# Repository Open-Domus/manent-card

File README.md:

# Manent card: hardware

Hardware design of the Manent card: a voice recorder with the outline of a payment card,
3.5 mm thick, that rides on the back of a phone or lies on the table in a meeting. A slide
switch starts it, a sensor lets it hear the phone it rides on, and the words reach the
phone as audio over Bluetooth LE. It is the
sibling of the ring in `manent-ring` and of the band in `manent-band`, in the form of the
Plaud Note and of Amazon's Bee Eclipse. Firmware and radio protocol live in the
`mnemo-band` repository.

Public page: [manentlabs.it/en/card/](https://manentlabs.it/en/card/) (English), [manentlabs.it/card/](https://manentlabs.it/card/) (Italian).

Nothing here has been built or measured. This is a first design on paper, checked by
scripts. Its choices are made and each says what would overturn it.

| What | Where |
| --- | --- |
| Design document: requirements, architecture, decisions | [docs/design.md](docs/design.md) |
| Does it fit? Card, the two stacks, cell, board area | [docs/space-budget.md](docs/space-budget.md) |
| How long does it last? | [docs/power-budget.md](docs/power-budget.md) |
| What it costs to make | [docs/cost-estimate.md](docs/cost-estimate.md) |
| Design review: what was checked, what was wrong, what is at risk | [docs/review.md](docs/review.md) |
| What the firmware must do for this hardware | [docs/firmware-requirements.md](docs/firmware-requirements.md) |
| What was decided and why, what is unknown, and what would settle it | [docs/open-questions.md](docs/open-questions.md) |
| Parts with sizes and how far each is verified | [parts/parts.yaml](parts/parts.yaml) |
| Circuit, as data | [electrical/gen/design.py](electrical/gen/design.py) |
| Schematic (KiCad 10), PDF, bill of materials | `electrical/kicad/`, `electrical/out/` |
| Board: placed and routed by script, no rule broken, nothing open | `electrical/kicad/card.kicad_pcb`, `electrical/out/board-*.svg` |
| Fit model, drawings, STEP | `mechanical/`, `mechanical/out/` |

## Build

Needs `uv`, and either KiCad 10 or Docker (`docker pull kicad/kicad:10.0`).

```
make all        # schematic, board, checks, tests, fit report, drawings, budgets, STEP
make test       # tests only
make route      # route the board again: needs Java and Freerouting, see tools/route.sh
```

The schematic and the board are generated: edit `electrical/gen/design.py` and the fit
model, never the `.kicad_sch` or `.kicad_pcb` files.
Every pin carries a label with its net name instead of drawn wires. `make schematic` runs
KiCad's rule check and compares the netlist KiCad reads with the one in `design.py`.

The board is placed and routed by script. `make board` rebuilds it from the route kept in
`electrical/kicad/card.ses`; after a change to the circuit or the placement that route no
longer fits and `make route` must be run. Nobody has reviewed the routing by eye.

## Licences

Hardware and the scripts that generate it under CERN-OHL-S v2 (`LICENSE`), documents under
CC BY-SA 4.0 (`LICENSE-docs`).

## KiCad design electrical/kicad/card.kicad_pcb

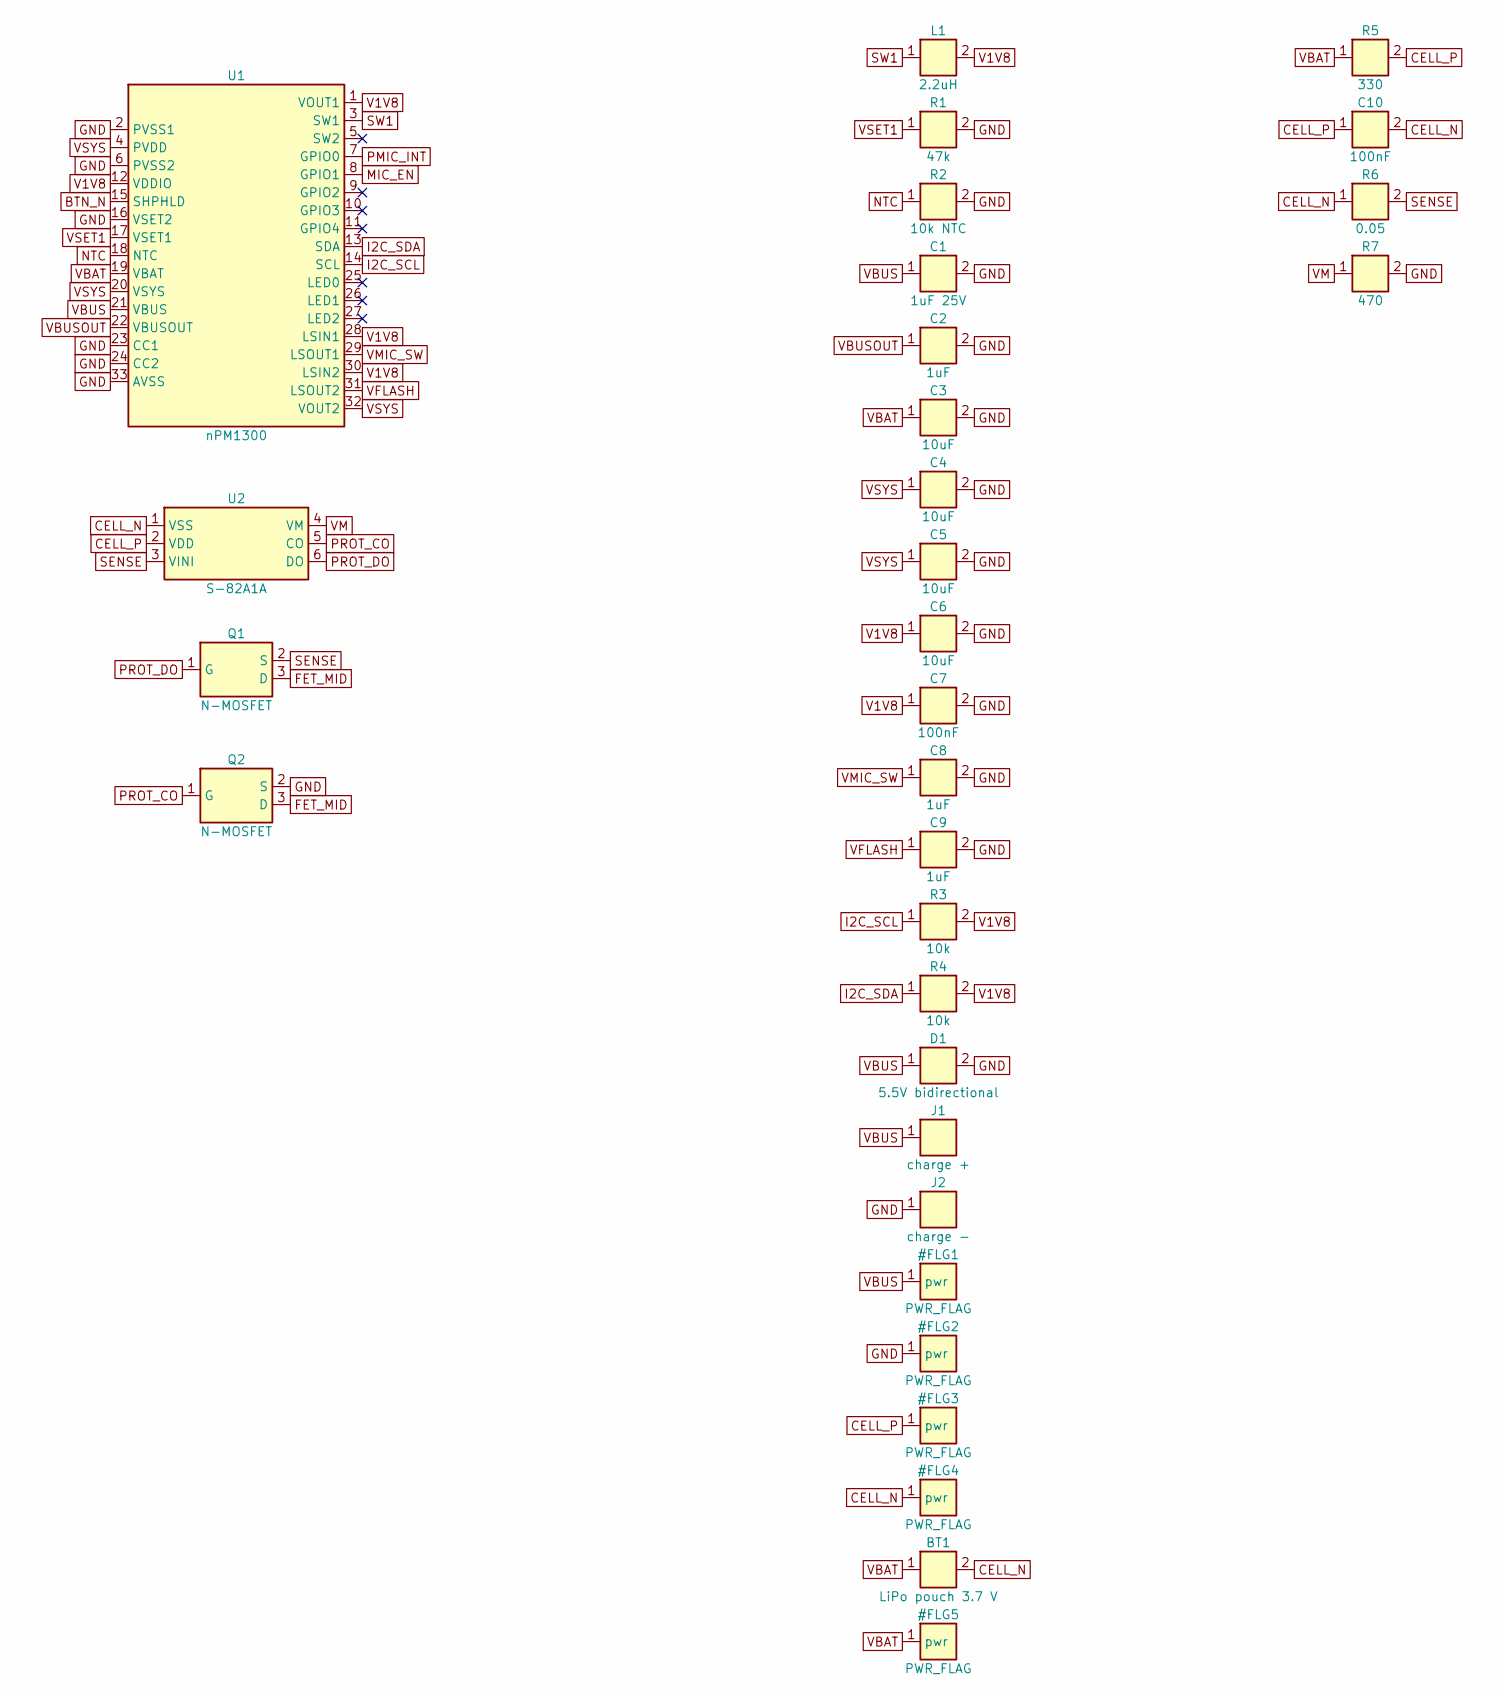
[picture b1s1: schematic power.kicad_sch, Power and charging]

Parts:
BT1: LiPo pouch 3.7 V; Cell_Tabs; MPN 203580 class
C1: 1uF 25V; C_0603_1608Metric
C2, C8, C9: 1uF; C_0402_1005Metric
C3, C4, C5, C6: 10uF; C_0603_1608Metric
C7, C10: 100nF; C_0402_1005Metric
D1: 5.5V bidirectional; D_0201_0603Metric; MPN ESD230-B1-W0201
J1: charge +; Pad_Contact_D2.0
J2: charge -; Pad_Contact_D2.0
L1: 2.2uH; L_0805_2012Metric; MPN VLS201610HBX-2R2M-1
Q1, Q2: N-MOSFET; SOT-883; MPN PMZB290UNE2
R1: 47k; R_0402_1005Metric
R2: 10k NTC; R_0402_1005Metric; MPN to choose
R3, R4: 10k; R_0402_1005Metric
R5: 330; R_0402_1005Metric
R6: 0.05; R_0402_1005Metric
R7: 470; R_0402_1005Metric
U1: nPM1300; QFN-32-1EP_5x5mm_P0.5mm_EP3.45x3.45mm; MPN nPM1300-QEAA-R7
U2: S-82A1A; DFN-6_1414; MPN S-82A1AAG-A6T5S (variant to confirm)

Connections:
BTN_N: U1.15 (SHPHLD); also elsewhere on the board
CELL_N: BT1.2, C10.2, R6.1, U2.1 (VSS)
CELL_P: C10.1, R5.2, U2.2 (VDD)
FET_MID: Q1.3 (D), Q2.3 (D)
GND: C1.2, C2.2, C3.2, C4.2, C5.2, C6.2, C7.2, C8.2, C9.2, D1.2, J2.1, Q2.2 (S), R1.2, R2.2, R7.2, U1.2 (PVSS1), U1.6 (PVSS2), U1.16 (VSET2), U1.23 (CC1), U1.24 (CC2), U1.33 (AVSS); also elsewhere on the board
I2C_SCL: R3.1, U1.14 (SCL); also elsewhere on the board
I2C_SDA: R4.1, U1.13 (SDA); also elsewhere on the board
MIC_EN: U1.8 (GPIO1); also elsewhere on the board
NTC: R2.1, U1.18 (NTC)
PMIC_INT: U1.7 (GPIO0); also elsewhere on the board
PROT_CO: Q2.1 (G), U2.5 (CO)
PROT_DO: Q1.1 (G), U2.6 (DO)
SENSE: Q1.2 (S), R6.2, U2.3 (VINI)
SW1: L1.1, U1.3 (SW1)
V1V8: C6.1, C7.1, L1.2, R3.2, R4.2, U1.1 (VOUT1), U1.12 (VDDIO), U1.28 (LSIN1), U1.30 (LSIN2); also elsewhere on the board
VBAT: BT1.1, C3.1, R5.1, U1.19 (VBAT); also elsewhere on the board
VBUS: C1.1, D1.1, J1.1, U1.21 (VBUS); also elsewhere on the board
VBUSOUT: C2.1, U1.22 (VBUSOUT)
VFLASH: C9.1, U1.31 (LSOUT2); also elsewhere on the board
VM: R7.1, U2.4 (VM)
VMIC_SW: C8.1, U1.29 (LSOUT1); also elsewhere on the board
VSET1: R1.1, U1.17 (VSET1)
VSYS: C4.1, C5.1, U1.4 (PVDD), U1.20 (VSYS), U1.32 (VOUT2); also elsewhere on the board

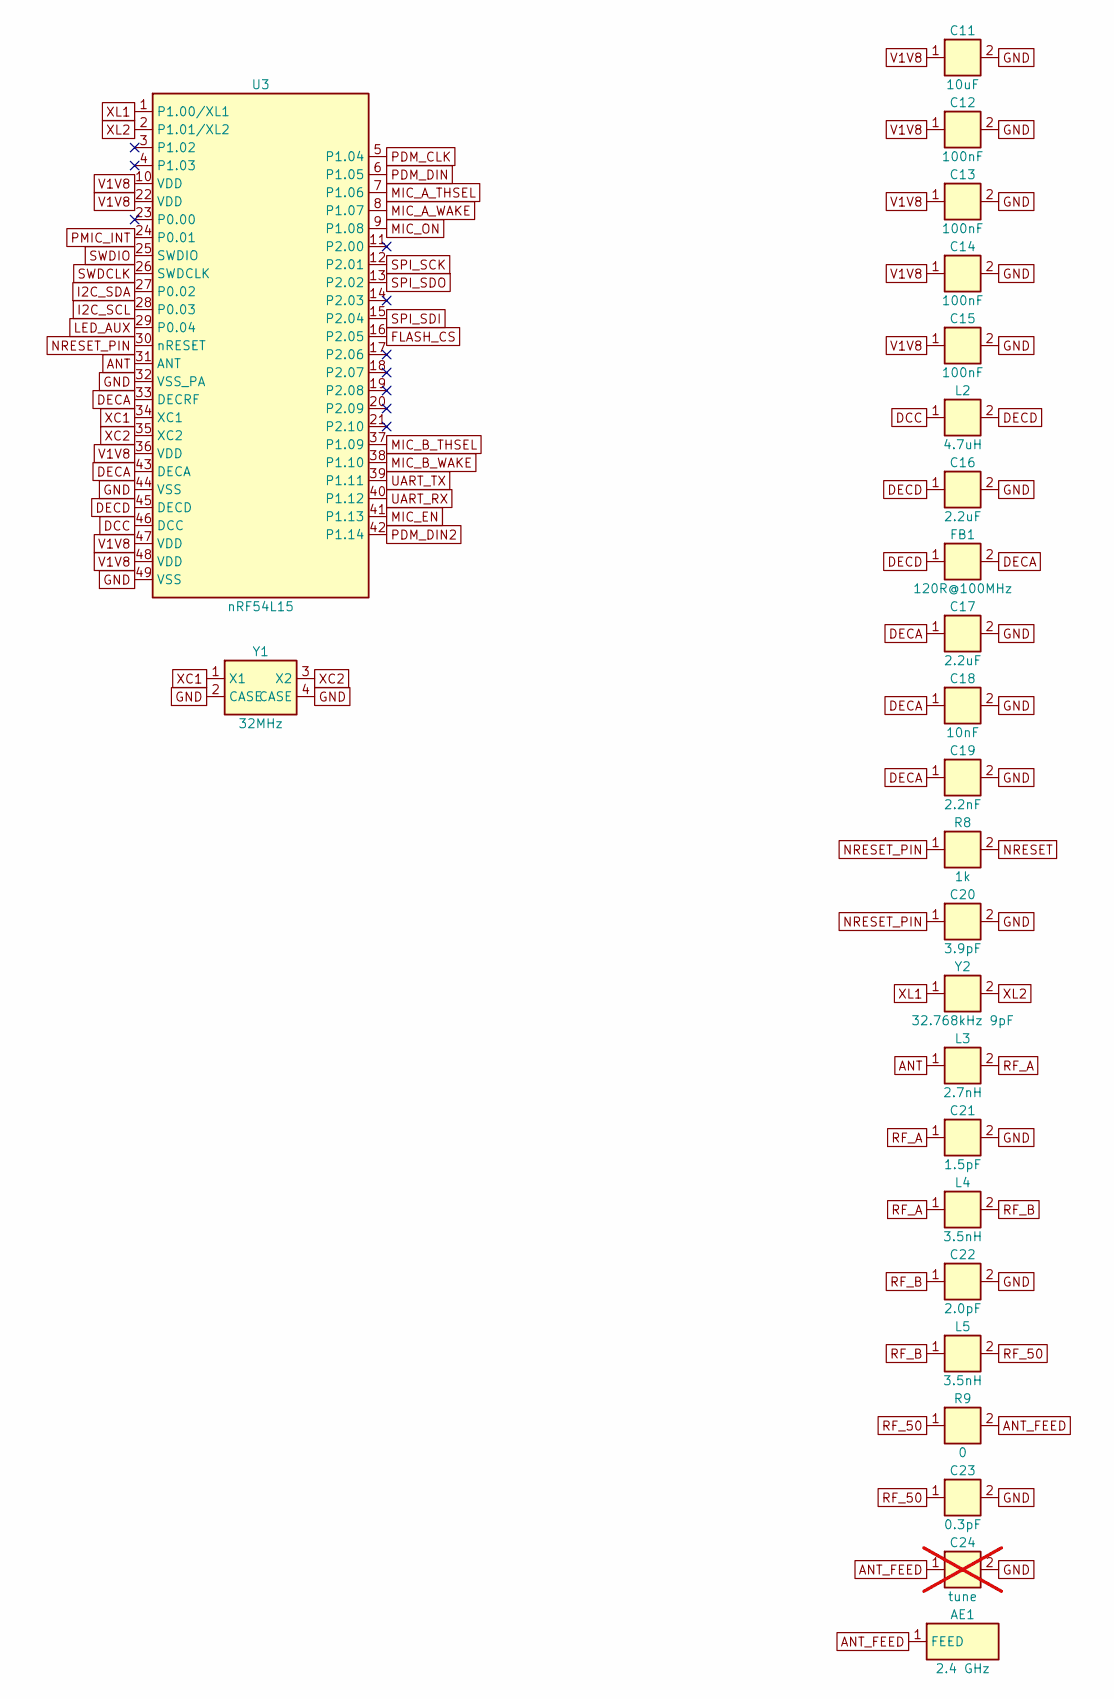
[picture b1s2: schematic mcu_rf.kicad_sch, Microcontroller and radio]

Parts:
AE1: 2.4 GHz; Antenna_1608; MPN ANT1608LL14R2400A
C11: 10uF; C_0603_1608Metric
C12, C13, C14, C15: 100nF; C_0201_0603Metric
C16, C17: 2.2uF; C_0201_0603Metric
C18: 10nF; C_0201_0603Metric
C19: 2.2nF; C_0201_0603Metric
C20: 3.9pF; C_0201_0603Metric
C21: 1.5pF; C_0201_0603Metric; MPN GJM0335C1E1R5WB01
C22: 2.0pF; C_0201_0603Metric; MPN GJM0335C1E2R0WB01
C23: 0.3pF; C_0201_0603Metric
C24: tune; C_0201_0603Metric; not fitted
FB1: 120R@100MHz; L_0201_0603Metric; MPN BLM03AG121SN1D
L2: 4.7uH; L_0402_1005Metric; MPN PLEA67BCA4R7M-1PT00
L3: 2.7nH; L_0201_0603Metric; MPN LQP03HQ2N7B02
L4, L5: 3.5nH; L_0201_0603Metric; MPN LQP03HQ3N5B02
R8: 1k; R_0201_0603Metric
R9: 0; R_0201_0603Metric
U3: nRF54L15; QFN-48-1EP_6x6mm_P0.4mm_EP4.6x4.6mm; MPN nRF54L15-QFAA-R
Y1: 32MHz; Crystal_SMD_2016-4Pin_2.0x1.6mm; MPN CX2016DB32000D0FLJCC
Y2: 32.768kHz 9pF; Crystal_SMD_2012-2Pin_2.0x1.2mm; MPN 9HT11-32.768KDZC-T

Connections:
ANT: L3.1, U3.31 (ANT)
ANT_FEED: AE1.1, C24.1, R9.2
DCC: L2.1, U3.46 (DCC)
DECA: C17.1, C18.1, C19.1, FB1.2, U3.33 (DECRF), U3.43 (DECA)
DECD: C16.1, FB1.1, L2.2, U3.45 (DECD)
FLASH_CS: U3.16 (P2.05); also elsewhere on the board
GND: C11.2, C12.2, C13.2, C14.2, C15.2, C16.2, C17.2, C18.2, C19.2, C20.2, C21.2, C22.2, C23.2, C24.2, U3.32 (VSS_PA), U3.44 (VSS), U3.49 (VSS), Y1.2 (CASE), Y1.4 (CASE); also elsewhere on the board
I2C_SCL: U3.28 (P0.03); also elsewhere on the board
I2C_SDA: U3.27 (P0.02); also elsewhere on the board
LED_AUX: U3.29 (P0.04); also elsewhere on the board
MIC_A_THSEL: U3.7 (P1.06); also elsewhere on the board
MIC_A_WAKE: U3.8 (P1.07); also elsewhere on the board
MIC_B_THSEL: U3.37 (P1.09); also elsewhere on the board
MIC_B_WAKE: U3.38 (P1.10); also elsewhere on the board
MIC_EN: U3.41 (P1.13); also elsewhere on the board
MIC_ON: U3.9 (P1.08); also elsewhere on the board
NRESET: R8.2; also elsewhere on the board
NRESET_PIN: C20.1, R8.1, U3.30 (nRESET)
PDM_CLK: U3.5 (P1.04); also elsewhere on the board
PDM_DIN: U3.6 (P1.05); also elsewhere on the board
PDM_DIN2: U3.42 (P1.14); also elsewhere on the board
PMIC_INT: U3.24 (P0.01); also elsewhere on the board
RF_50: C23.1, L5.2, R9.1
RF_A: C21.1, L3.2, L4.1
RF_B: C22.1, L4.2, L5.1
SPI_SCK: U3.12 (P2.01); also elsewhere on the board
SPI_SDI: U3.15 (P2.04); also elsewhere on the board
SPI_SDO: U3.13 (P2.02); also elsewhere on the board
SWDCLK: U3.26 (SWDCLK); also elsewhere on the board
SWDIO: U3.25 (SWDIO); also elsewhere on the board
UART_RX: U3.40 (P1.12); also elsewhere on the board
UART_TX: U3.39 (P1.11); also elsewhere on the board
V1V8: C11.1, C12.1, C13.1, C14.1, C15.1, U3.10 (VDD), U3.22 (VDD), U3.36 (VDD), U3.47 (VDD), U3.48 (VDD); also elsewhere on the board
XC1: U3.34 (XC1), Y1.1 (X1)
XC2: U3.35 (XC2), Y1.3 (X2)
XL1: U3.1 (P1.00/XL1), Y2.1
XL2: U3.2 (P1.01/XL2), Y2.2

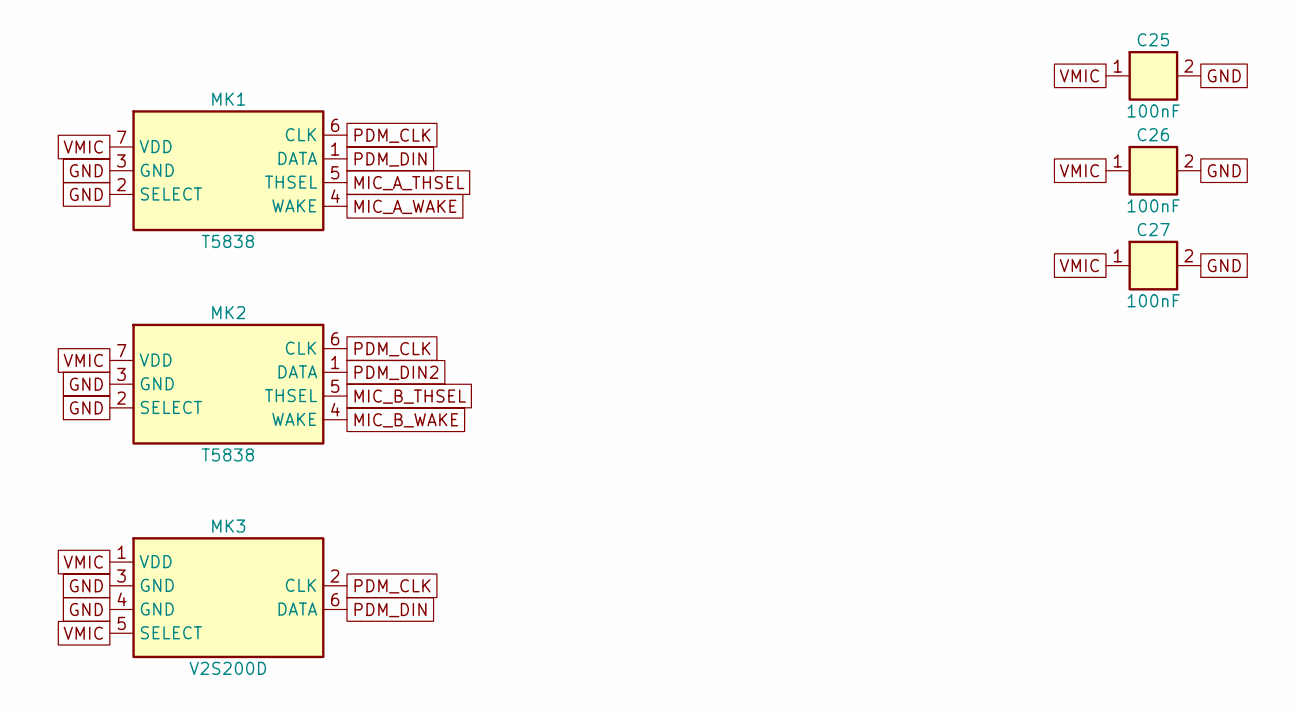
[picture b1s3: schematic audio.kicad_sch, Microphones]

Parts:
C25, C26, C27: 100nF; C_0201_0603Metric
MK1, MK2: T5838; MPN MMICT5838-00-012
MK3: V2S200D; MPN V2S200D

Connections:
GND: C25.2, C26.2, C27.2, MK1.2 (SELECT), MK1.3 (GND), MK2.2 (SELECT), MK2.3 (GND), MK3.3 (GND), MK3.4 (GND); also elsewhere on the board
MIC_A_THSEL: MK1.5 (THSEL); also elsewhere on the board
MIC_A_WAKE: MK1.4 (WAKE); also elsewhere on the board
MIC_B_THSEL: MK2.5 (THSEL); also elsewhere on the board
MIC_B_WAKE: MK2.4 (WAKE); also elsewhere on the board
PDM_CLK: MK1.6 (CLK), MK2.6 (CLK), MK3.2 (CLK); also elsewhere on the board
PDM_DIN: MK1.1 (DATA), MK3.6 (DATA); also elsewhere on the board
PDM_DIN2: MK2.1 (DATA); also elsewhere on the board
VMIC: C25.1, C26.1, C27.1, MK1.7 (VDD), MK2.7 (VDD), MK3.1 (VDD), MK3.5 (SELECT); also elsewhere on the board

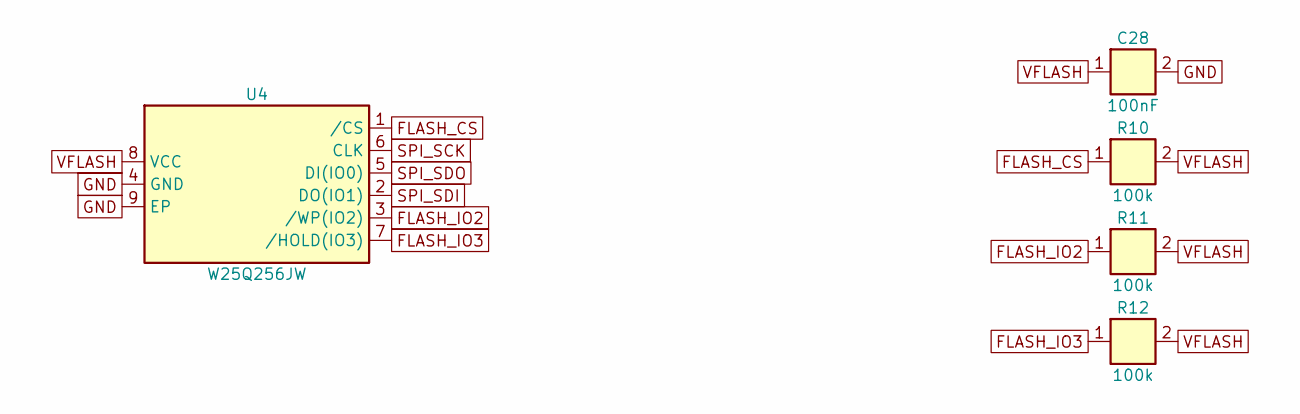
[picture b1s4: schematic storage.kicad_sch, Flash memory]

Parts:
C28: 100nF; C_0402_1005Metric
R10, R11, R12: 100k; R_0402_1005Metric
U4: W25Q256JW; WSON-8-1EP_8x6mm_P1.27mm_EP3.4x4.3mm; MPN W25Q256JWEIQ

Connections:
FLASH_CS: R10.1, U4.1 (/CS); also elsewhere on the board
FLASH_IO2: R11.1, U4.3 (/WP(IO2))
FLASH_IO3: R12.1, U4.7 (/HOLD(IO3))
GND: C28.2, U4.4 (GND), U4.9 (EP); also elsewhere on the board
SPI_SCK: U4.6 (CLK); also elsewhere on the board
SPI_SDI: U4.2 (DO(IO1)); also elsewhere on the board
SPI_SDO: U4.5 (DI(IO0)); also elsewhere on the board
VFLASH: C28.1, R10.2, R11.2, R12.2, U4.8 (VCC); also elsewhere on the board

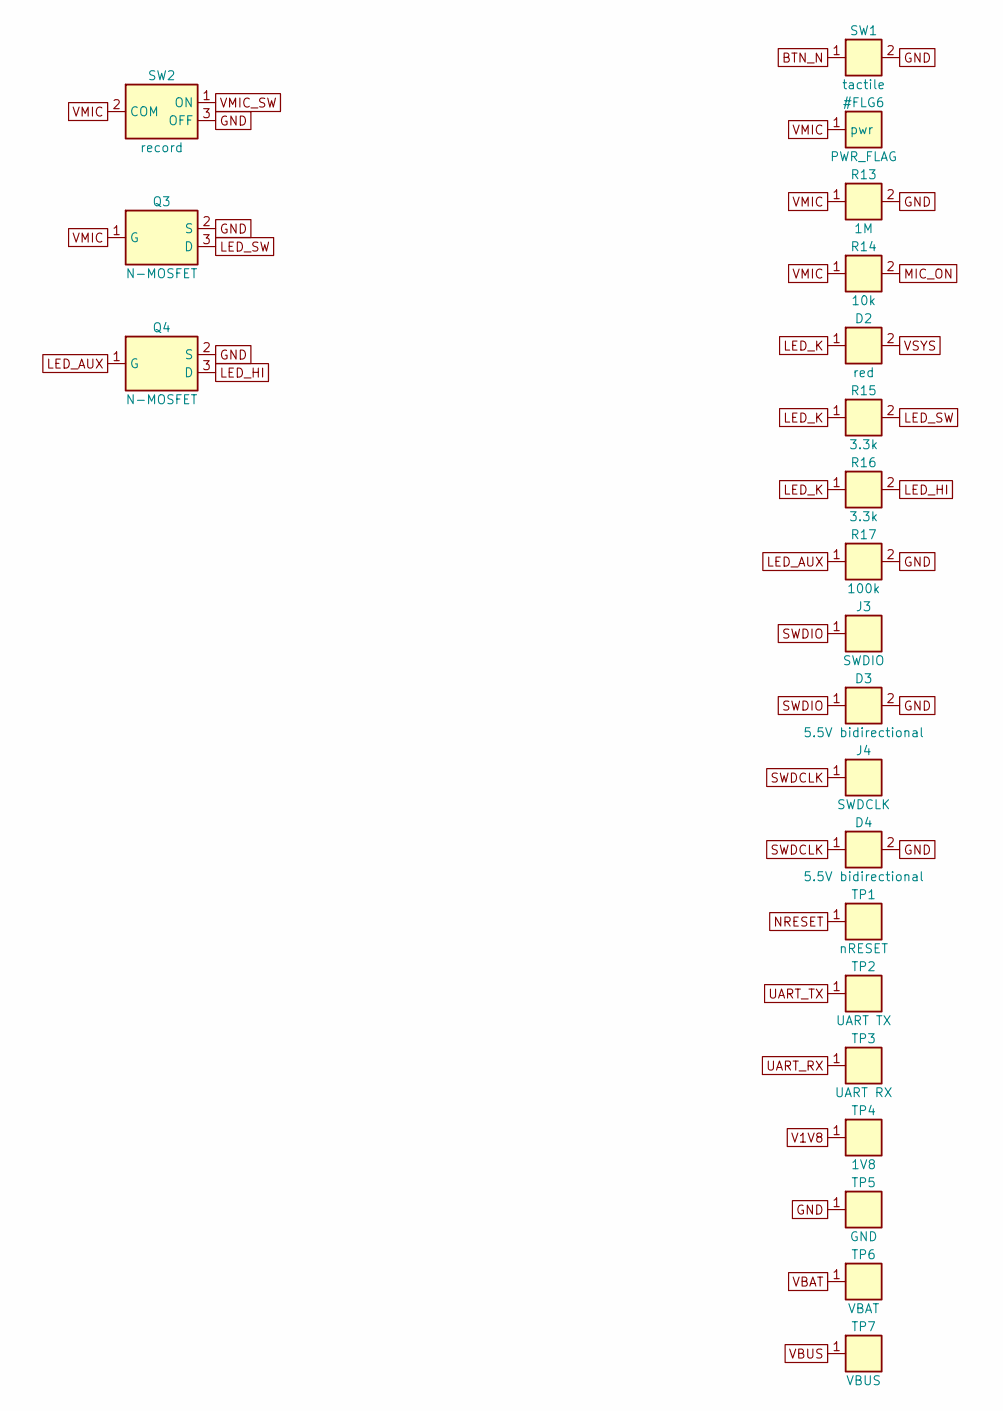
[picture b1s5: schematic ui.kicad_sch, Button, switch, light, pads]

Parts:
D2: red; LED_156125RS75000; MPN 156125RS75000
D3, D4: 5.5V bidirectional; D_0201_0603Metric; MPN ESD230-B1-W0201
J3: SWDIO; Pad_Contact_D2.0
J4: SWDCLK; Pad_Contact_D2.0
Q3, Q4: N-MOSFET; SOT-883; MPN PMZB290UNE2
R13: 1M; R_0402_1005Metric
R14: 10k; R_0402_1005Metric
R15, R16: 3.3k; R_0402_1005Metric
R17: 100k; R_0402_1005Metric
SW1: tactile; EVQP7J; MPN EVQP7J01P
SW2: record; SSSS811101; MPN SSSS811101
TP1: nRESET; Pad_Test_D1.0
TP2: UART TX; Pad_Test_D1.0
TP3: UART RX; Pad_Test_D1.0
TP4: 1V8; Pad_Test_D1.0
TP5: GND; Pad_Test_D1.0
TP6: VBAT; Pad_Test_D1.0
TP7: VBUS; Pad_Test_D1.0

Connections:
BTN_N: SW1.1; also elsewhere on the board
GND: D3.2, D4.2, Q3.2 (S), Q4.2 (S), R13.2, R17.2, SW1.2, SW2.3 (OFF), TP5.1; also elsewhere on the board
LED_AUX: Q4.1 (G), R17.1; also elsewhere on the board
LED_HI: Q4.3 (D), R16.2
LED_K: D2.1, R15.1, R16.1
LED_SW: Q3.3 (D), R15.2
MIC_ON: R14.2; also elsewhere on the board
NRESET: TP1.1; also elsewhere on the board
SWDCLK: D4.1, J4.1; also elsewhere on the board
SWDIO: D3.1, J3.1; also elsewhere on the board
UART_RX: TP3.1; also elsewhere on the board
UART_TX: TP2.1; also elsewhere on the board
V1V8: TP4.1; also elsewhere on the board
VBAT: TP6.1; also elsewhere on the board
VBUS: TP7.1; also elsewhere on the board
VMIC: Q3.1 (G), R13.1, R14.1, SW2.2 (COM); also elsewhere on the board
VMIC_SW: SW2.1 (ON); also elsewhere on the board
VSYS: D2.2; also elsewhere on the board

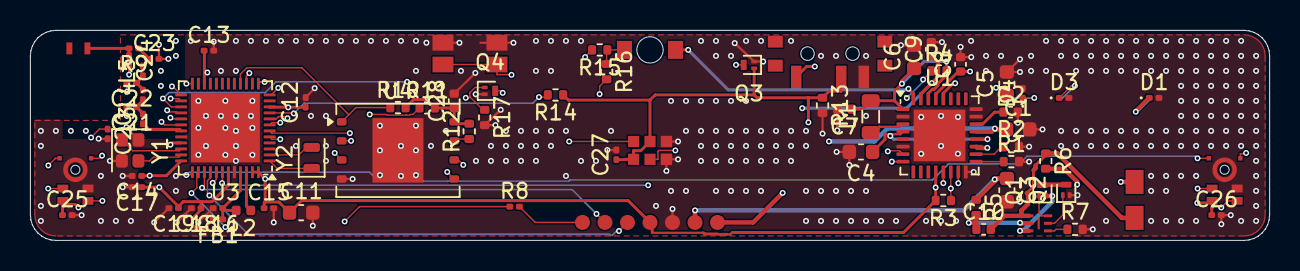
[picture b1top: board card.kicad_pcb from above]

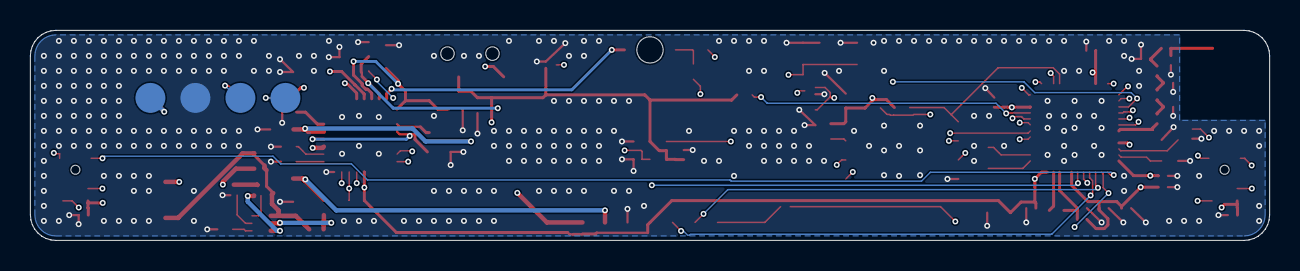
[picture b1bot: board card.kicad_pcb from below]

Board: 4 copper layers, 82.6 x 14.0 mm, 83 parts (4 on the bottom side), 60 nets.

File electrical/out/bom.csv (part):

References,Quantity,Value,Manufacturer,Part number,Package,Fitted,Notes
U1,1,nPM1300,Nordic Semiconductor,nPM1300-QEAA-R7,"QFN-32 5x5, 0.5 mm pitch",yes,"The band's nPM1304 stops at 100 mA; this one charges at 32 to 800 mA and has the same 32 pins. Set about 225 mA, half the cell's capacity per hour. BUCK2 unused as in Nordic's reference configuration 2 (nPM1304 layout files; the same in the nPM1300's): VSET2 grounded, SW2 open, VOUT2 to VSYS. LED0-2, GPIO2-4 left open: not confirmed. CC1 and CC2 grounded: the input limit starts at 100 mA and firmware must raise it each time the charger is connected"
L1,1,2.2uH,TDK,VLS201610HBX-2R2M-1,0806,yes,"Nordic asks for DCR under 0.4 ohm in 0806 (2.0 x 1.6 mm); this one is 0.17 max, 1.45 A, 1.0 tall. The same part on the band, the card and the pendant"
R1,1,47k,,,0402,yes,Sets BUCK1 to 1.8 V at power-on
R2,1,10k NTC,,to choose,0402,yes,"Thermistor, B about 3380 K, placed by the cell tabs: stops the charge when the closed card is too warm or too cold"
C1,1,1uF 25V,,,0603,yes,"As Nordic's nPM1304-QEAA reference layout 1.0, configuration 2, the sibling chip with the same pins"
C2 C8 C9,3,1uF,,,0402,yes,"As Nordic's nPM1304-QEAA reference layout 1.0, configuration 2, the sibling chip with the same pins | Load switch output, before the recording switch. As Nordic's nPM1304-QEAA reference layout 1.0, configuration 2, the sibling chip with the same pins | Load switch output. As Nordic's nPM1304-QEAA reference layout 1.0, configuration 2, the sibling chip with the same pins"
C3 C4 C5 C6 C11,5,10uF,,,0603,yes,"The nPM1304 reference has 2.2 uF here; kept at 10 uF for this card's 225 mA charge until the nPM1300's layout files are read | Buck input, at PVDD and PVSS1. As Nordic's nPM1304-QEAA reference layout 1.0, configuration 2, the sibling chip with the same pins | VSYS output. As Nordic's nPM1304-QEAA reference layout 1.0, configuration 2, the sibling chip with the same pins | Buck output: at least 4 uF effective. As Nordic's nPM1304-QEAA reference layout 1.0, configuration 2, the sibling chip with the same pins"
C7 C10 C28,3,100nF,,,0402,yes,VDDIO
R3 R4 R14,3,10k,,,0402,yes,"Lets the SoC read the switch and wake on it. With the switch off the rail is grounded, so this pin cannot power the microphones"
D1 D3 D4,3,5.5V bidirectional,Infineon,ESD230-B1-W0201,0201,yes,Fingers reach this pad. Its capacitance on a debug line is to confirm
J1,1,charge +,,,2 mm pad,yes,"Copper on the bare face of the board, behind a window in the front skin, at one end only: a card laid on its charger the wrong way round touches nothing"
J2,1,charge -,,,2 mm pad,yes,
BT1,1,LiPo pouch 3.7 V,to choose,203580 class,,yes,Size and capacity depend on the card; see docs/space-budget.md
R5,1,330,,,0402,yes,Protector supply filter
U2,1,S-82A1A,ABLIC,S-82A1AAG-A6T5S (variant to confirm),DFN-6 1.4x1.4,yes,Fit only if the cell has no protection of its own; thresholds to match the charge voltage
R6,1,0.05,,,0402,yes,"Overcurrent sense: about 1 A trip if the threshold is 50 mV (calculated, not from a datasheet). The band's 0.25 ohm would trip at 200 mA, below this card's 225 mA charge"
R7,1,470,,,0402,yes,
Q1 Q2 Q3 Q4,4,N-MOSFET,Nexperia,PMZB290UNE2,DFN1006B-3,yes,"Discharge FET; two singles with their drains joined. The same FET in all eight places of the four products | Charge FET | Gate is the microphone rail: the light is on whenever the microphones have power. Vgs(th) under 1 V | Firmware can only add light, never remove the recording light"
U3,1,nRF54L15,Nordic Semiconductor,nRF54L15-QFAA-R,"QFN-48 6x6, 0.4 mm pitch",yes,Pin 49 is the exposed pad: ground
C12 C13 C14 C15 C25 C26 C27,7,100nF,,,0201,yes,"One next to each side's VDD pin. As Nordic's nRF54L15-QFAA reference layout 0.8 | X7R, next to pin 7 of microphone A | X7R, next to pin 7 of microphone B | C0G, next to the supply pin of the call sensor: its maker asks for no class 2 ceramic nearby, which sings"
L2,1,4.7uH,TDK,PLEA67BCA4R7M-1PT00,0402,yes,"DC/DC inductor, the ring's part. Nordic's QFN reference takes a 0603 of 0.65 ohm and 120 mA; this one is 1.08 ohm max"
C16 C17,2,2.2uF,,,0201,yes,As Nordic's nRF54L15-QFAA reference layout 0.8
FB1,1,120R@100MHz,Murata,BLM03AG121SN1D,0201,yes,"The reference asks 120 ohm at 100 MHz, 200 mA, 0.5 ohm max: the ring's part"
C18,1,10nF,,,0201,yes,As Nordic's nRF54L15-QFAA reference layout 0.8
C19,1,2.2nF,,,0201,yes,X7R. As Nordic's nRF54L15-QFAA reference layout 0.8
R8,1,1k,,,0201,yes,"Filter on the reset pin, next to the antenna pin. As Nordic's nRF54L15-QFAA reference layout 0.8"
C20,1,3.9pF,,,0201,yes,"C0G, at the reset pin. As Nordic's nRF54L15-QFAA reference layout 0.8"
Y1,1,32MHz,Kyocera,CX2016DB32000D0FLJCC,2016,yes,"2.0 x 1.6 mm, 8 pF, 10 ppm, as the reference asks (8 pF, 40 ppm in all); pads 2 and 4 are the lid, grounded: check against its drawing. Load capacitors are inside the chip"
Y2,1,32.768kHz 9pF,TXC,9HT11-32.768KDZC-T,2012,yes,"Fitted, unlike on the ring: the card stays connected for weeks and there is room. Load capacitors are inside the chip"
L3,1,2.7nH,Murata,LQP03HQ2N7B02,0201,yes,Matching network. As Nordic's nRF54L15-QFAA reference layout 0.8
C21,1,1.5pF,Murata,GJM0335C1E1R5WB01,0201,yes,Matching network. As Nordic's nRF54L15-QFAA reference layout 0.8
L4 L5,2,3.5nH,Murata,LQP03HQ3N5B02,0201,yes,Matching network. As Nordic's nRF54L15-QFAA reference layout 0.8
C22,1,2.0pF,Murata,GJM0335C1E2R0WB01,0201,yes,Matching network. As Nordic's nRF54L15-QFAA reference layout 0.8
R9,1,0,,,0201,yes,"Antenna tuning, series: value from measurement in a closed card, alone and on a phone"
C23,1,0.3pF,,,0201,yes,"C0G, 0.1 pF tolerance: the last part of the matching network. As Nordic's nRF54L15-QFAA reference layout 0.8"
C24,1,tune,,,0201,no,"Antenna tuning, shunt"
AE1,1,2.4 GHz,Yageo,ANT1608LL14R2400A,1608 chip antenna,yes,Chip antenna or printed trace in the corner of the board; decided with the first radio measurements
MK1 MK2,2,T5838,TDK InvenSense,MMICT5838-00-012,3.5x2.65x0.98 bottom port,yes,"Microphone A, at one end of the board, on data line PDM_DIN. No pull resistor on DATA. Board hole 0.5-1.0 mm under the port: the sound comes through the board | Microphone B, at the opposite end, on data line PDM_DIN2. No pull resistor on DATA. Board hole 0.5-1.0 mm under the port: the sound comes through the board"
MK3,1,V2S200D,Syntiant,V2S200D,3.3x2.3x0.93 LGA-6,yes,"Hears the phone through its back: the far side of a call. On the microphones' rail, so the switch and the light govern it too. Shares data line 1 with microphone A: SELECT at the rail makes it speak on the rising clock edge (datasheet table 7); that microphone A speaks on the falling one is to confirm. 290 uA at this clock, asleep when the clock is held low. Senses along Z, across the board. It measures how its own body shakes: the board under it must be fixed stiffly to the back skin, with a post or a bead of hard adhesive next to it"
U4,1,W25Q256JW,Winbond,W25Q256JWEIQ,WSON-8 8x6,yes,"256 Mbit NOR at 1.8 V in 8-WSON 8x6, from a distributor listing; pin order and height not read. The 512 Mbit and 1 Gbit parts of the family fit the same pads and cost three and ten times as much. Needs four-byte addresses. Exposed pad to ground is the usual practice, to confirm. Any 1.8 V serial NOR in this package fits"
R10 R11 R12 R17,4,100k,,,0402,yes,Keeps the chip deselected while the rail rises | Termination in single-bit SPI to confirm | Off while the SoC is in reset
SW1,1,tactile,Panasonic,EVQP7J01P,side-push 3.5x2.9x1.35,yes,"Pressed from the edge of the card; pulled up inside the PMIC (SHPHLD). 1.6 N, stands 30 N; works down to 10 uA. The SoC learns of presses from the PMIC interrupt, as on the ring"
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
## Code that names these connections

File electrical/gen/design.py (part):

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TVS = two_pin("TVS", "D")
PAD = SymDef("PAD", "TP", (Pin("1", "~", "passive", "L"),), width=5.08)
CONTACT = SymDef("CONTACT", "J", (Pin("1", "~", "passive", "L"),), width=5.08)
ANT = SymDef("ANTENNA", "AE", (Pin("1", "FEED", "passive", "L"),), width=10.16)
FLAG = SymDef("PWR_FLAG", "#FLG", (Pin("1", "pwr", "power_out", "L"),), width=5.08, virtual=True)
NFET = ic("NMOS", "Q", "1 G i L\n2 S p R\n3 D p R", width=10.16)

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4 PVDD pi L
5 SW2 p R
6 PVSS2 pi L
7 GPIO0 b R
8 GPIO1 b R
9 GPIO2 b R
10 GPIO3 b R
11 GPIO4 b R
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        "VSYS": "VSYS", "PVDD": "VSYS", "VDDIO": "V1V8", "AVSS": "GND", "PVSS1": "GND", "PVSS2": "GND",
        "VSET1": "VSET1", "VSET2": "GND", "SHPHLD": "BTN_N", "SW1": "SW1", "VOUT1": "V1V8",
        "VOUT2": "VSYS", "LSIN1": "V1V8", "LSOUT1": "VMIC_SW", "LSIN2": "V1V8", "LSOUT2": "VFLASH",
        "SCL": "I2C_SCL", "SDA": "I2C_SDA", "GPIO0": "PMIC_INT", "GPIO1": "MIC_EN",
    }), mpn="nPM1300-QEAA-R7", mfr="Nordic Semiconductor", package="QFN-32 5x5, 0.5 mm pitch",
        note="The band's nPM1304 stops at 100 mA; this one charges at 32 to 800 mA and has the same 32 pins. "
             "Set about 225 mA, half the cell's capacity per hour. "
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    add(SOC, "nRF54L15", "mcu_rf", by_name(SOC, {
        "VDD": "V1V8", "DCC": "DCC", "DECD": "DECD", "DECA": "DECA", "DECRF": "DECA",
        "VSS": "GND", "VSS_PA": "GND", "XC1": "XC1", "XC2": "XC2", "ANT": "ANT",
        "nRESET": "NRESET_PIN", "SWDCLK": "SWDCLK", "SWDIO": "SWDIO", **SOC_NETS,
    }), mpn="nRF54L15-QFAA-R", mfr="Nordic Semiconductor", package="QFN-48 6x6, 0.4 mm pitch",
        note="Pin 49 is the exposed pad: ground")
    cap("10uF", "V1V8", "mcu_rf", pkg="0603")
    for _ in range(4):
        cap("100nF", "V1V8", "mcu_rf", pkg="0201", note="One next to each side's VDD pin. " + REF)
    add(L, "4.7uH", "mcu_rf", ("DCC", "DECD"), mpn="PLEA67BCA4R7M-1PT00", mfr="TDK", package="0402",
        note="DC/DC inductor, the ring's part. Nordic's QFN reference takes a 0603 of 0.65 ohm and 120 mA; this one is 1.08 ohm max")
    cap("2.2uF", "DECD", "mcu_rf", pkg="0201", note=REF)
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    cap("2.2uF", "DECA", "mcu_rf", pkg="0201", note=REF)
    cap("10nF", "DECA", "mcu_rf", pkg="0201", note=REF)
    cap("2.2nF", "DECA", "mcu_rf", pkg="0201", note="X7R. " + REF)
    res("1k", "NRESET_PIN", "NRESET", "mcu_rf", pkg="0201", note="Filter on the reset pin, next to the antenna pin. " + REF)
    cap("3.9pF", "NRESET_PIN", "mcu_rf", pkg="0201", note="C0G, at the reset pin. " + REF)
    add(XTAL4, "32MHz", "mcu_rf", {"1": "XC1", "3": "XC2", "2": "GND", "4": "GND"}, mpn="CX2016DB32000D0FLJCC", mfr="Kyocera", package="2016",
        note="2.0 x 1.6 mm, 8 pF, 10 ppm, as the reference asks (8 pF, 40 ppm in all); pads 2 and 4 are the lid, grounded: check against its drawing. "
             "Load capacitors are inside the chip")
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            mpn="MMICT5838-00-012", mfr="TDK InvenSense", package="3.5x2.65x0.98 bottom port",
            note=f"Microphone {name}, at {where}, on data line {data}. "
                 "No pull resistor on DATA. Board hole 0.5-1.0 mm under the port: the sound comes through the board")
        cap("100nF", "VMIC", "audio", pkg="0201", note=f"X7R, next to pin 7 of microphone {name}")

    add(VPS, "V2S200D", "audio", by_name(VPS, {"VDD": "VMIC", "GND": "GND", "SELECT": "VMIC", "CLK": "PDM_CLK", "DATA": "PDM_DIN"}),
        mpn="V2S200D", mfr="Syntiant", package="3.3x2.3x0.93 LGA-6",
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             "290 uA at this clock, asleep when the clock is held low. Senses along Z, across the board. "
             "It measures how its own body shakes: the board under it must be fixed stiffly to the back skin, "
             "with a post or a bead of hard adhesive next to it")
    cap("100nF", "VMIC", "audio", pkg="0201", note="C0G, next to the supply pin of the call sensor: its maker asks for no class 2 ceramic nearby, which sings")

    # ---- flash ---------------------------------------------------------------------------
    add(FLASH, "W25Q256JW", "storage", by_name(FLASH, {
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    add(SW, "tactile", "ui", ("BTN_N", "GND"), mpn="EVQP7J01P", mfr="Panasonic", package="side-push 3.5x2.9x1.35",
        note="Pressed from the edge of the card; pulled up inside the PMIC (SHPHLD). 1.6 N, stands 30 N; works down to 10 uA. "
             "The SoC learns of presses from the PMIC interrupt, as on the ring")
    add(SPDT, "record", "ui", {"2": "VMIC", "1": "VMIC_SW", "3": "GND"}, mpn="SSSS811101", mfr="Alps Alpine", package="slide 6.7x2.6x1.4",
        note="The recording switch. It is in the microphones' supply itself: in the off position the microphones "
             "have no power and their rail is held at ground, whatever the firmware does. Terminal 2 is the common. "
             "Rated down to 50 uA at 3 V; here it carries about 1.3 mA at 1.8 V")
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    add(NFET, "N-MOSFET", "ui", {"1": "LED_AUX", "2": "GND", "3": "LED_HI"}, mpn="PMZB290UNE2", mfr="Nexperia", package="DFN1006B-3",
        note="Firmware can only add light, never remove the recording light")
    res("100k", "LED_AUX", "GND", "ui", note="Off while the SoC is in reset")
    for label, net in (("SWDIO", "SWDIO"), ("SWDCLK", "SWDCLK")):
        add(CONTACT, label, "ui", (net,), package="2 mm pad",
            note="Service pad next to the charging pads: reachable with the card closed")
        add(TVS, "5.5V bidirectional", "ui", (net, "GND"), mpn="ESD230-B1-W0201", mfr="Infineon", package="0201",
            note="Fingers reach this pad. Its capacitance on a debug line is to confirm")
    for label, net in (("nRESET", "NRESET"), ("UART TX", "UART_TX"), ("UART RX", "UART_RX"), ("1V8", "V1V8"),
                       ("GND", "GND"), ("VBAT", "VBAT"), ("VBUS", "VBUS")):
        add(PAD, label, "ui", (net,), note="Test pad on the board, for the factory test before the card is closed")
    for c in comps:
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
